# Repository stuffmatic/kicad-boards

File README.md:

# KiCad boards

This is a collection of mostly audio related dev boards designed in KiCad. The KiCad files are released under the [CC-BY-SA license](https://creativecommons.org/licenses/by-sa/4.0/).

## Board folders

Each board folder contains relevant datasheets along with [JLCPCB](https://jlcpcb.com/) fabrication files for PCB manufacturing and SMD assembly. Some additional easy hand soldering of connectors and headers may be required as indicated in the board description.

* [ap3722at\_mic\_breakout](ap3722at_mic_breakout) - Analog mono MEMS microphone breakout board.
* [bq24072\_pmic\_board](bq24072_pmic_board) - Power-path management and battery charger board.
* [pcm5102a\_codec\_breakout](pcm5102a_codec_breakout) - Audio codec breakout board.
* [tpa2012d2\_amp\_breakout](tpa2012d2_amp_breakout) - Class-D stereo audio power amplifier breakout board.
* [wm8758b\_codec\_breakout](wm8758b_codec_breakout) - Audio codec breakout board.
* [wm8904\_codec\_breakout](wm8904_codec_breakout) - Audio codec breakout board.

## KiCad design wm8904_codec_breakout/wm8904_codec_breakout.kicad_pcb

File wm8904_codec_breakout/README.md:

# WM8904 audio codec breakout board

A breakout board for the [WM8904 audio codec](datasheets/1912111437_Cirrus-Logic-WM8904CGEFL-RV_C323845.pdf) with 3.5mm microphone input and line/headphone output jacks.

## Pinout

* __VDD__ - Supply voltage,  3.3V - 12V 
* __GND__ - Ground
* __1V8__ - 1.8V codec supply voltage. Should typically not be connected.

See [datasheeet](datasheets/1912111437_Cirrus-Logic-WM8904CGEFL-RV_C323845.pdf) for the other pins.

## Connectors

* __MIC__ - Stereo microphone input
* __HP__ - Line/headphone output

## Hand soldered components

* 1x12 2.54 mm headers
* 1x12 2.54 mm headers

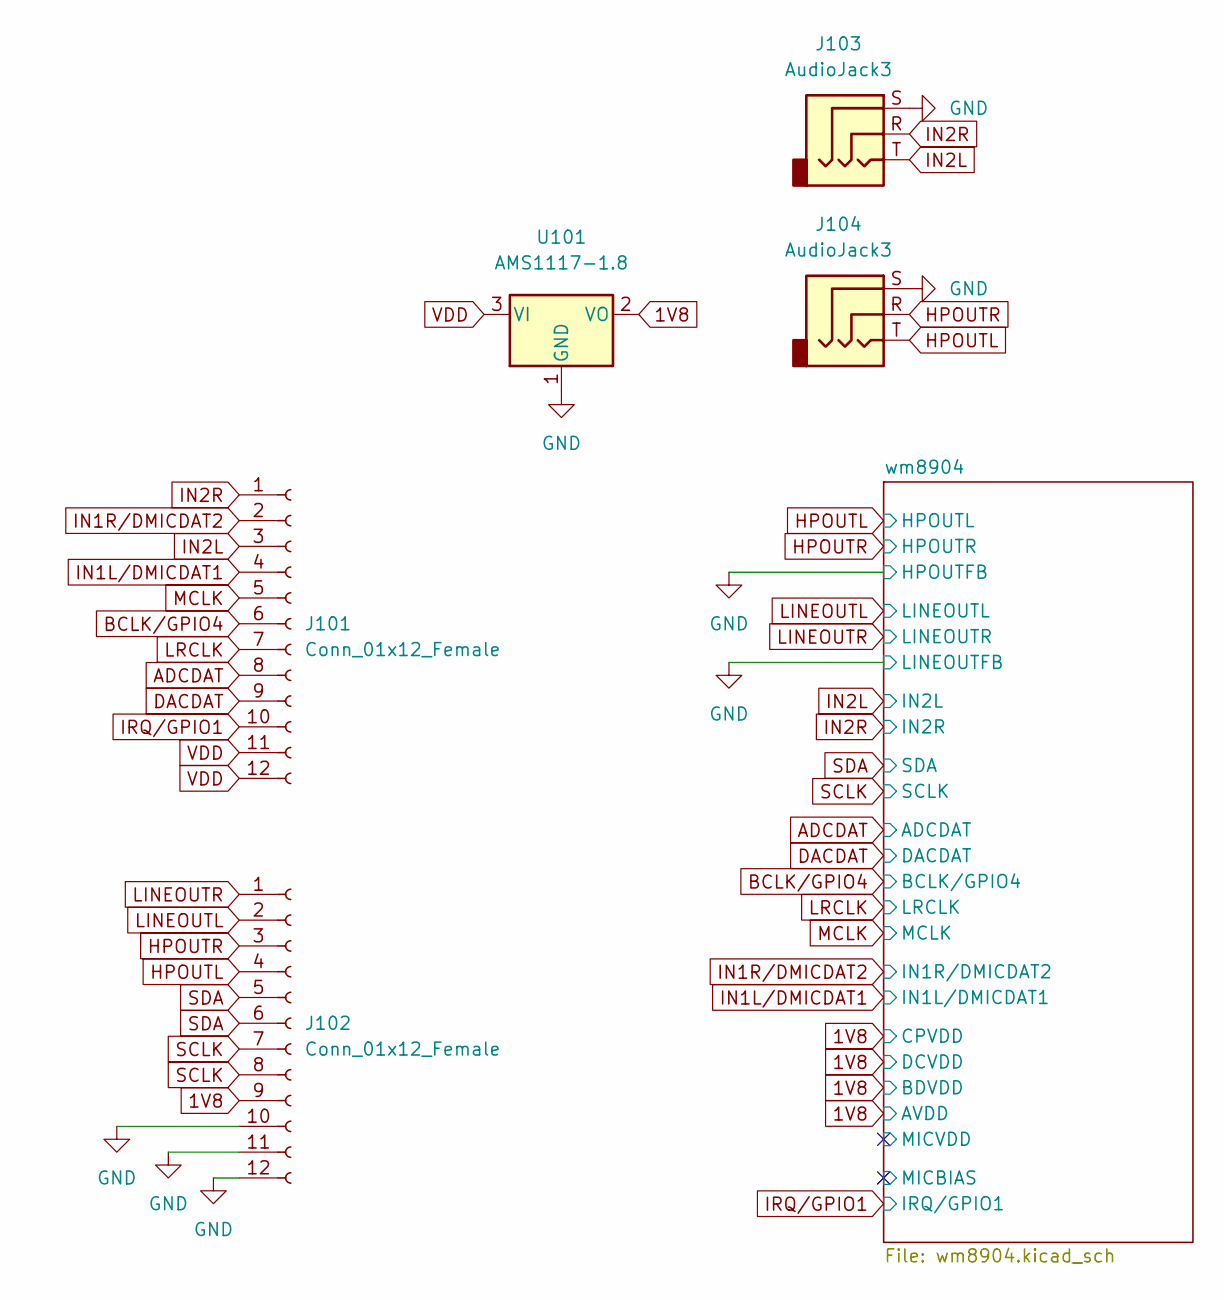
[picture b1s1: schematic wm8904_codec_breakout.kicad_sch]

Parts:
J101, J102: Conn_01x12_Female; PinSocket_1x12_P2.54mm_Vertical; JLCPCB BOM False
J103, J104: AudioJack3; PJ-320B-3A; LCSC Part C707224
U101: AMS1117-1.8; SOT-223-3_TabPin2; LCSC Part C6185

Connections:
1V8: J102.9, U101.2 (VO); also elsewhere on the board
ADCDAT: J101.8; also elsewhere on the board
BCLK/GPIO4: J101.6; also elsewhere on the board
DACDAT: J101.9; also elsewhere on the board
GND: J102.10, J102.11, J102.12, J103.S, J104.S, U101.1 (GND); also elsewhere on the board
HPOUTL: J102.4, J104.T; also elsewhere on the board
HPOUTR: J102.3, J104.R; also elsewhere on the board
IN1L/DMICDAT1: J101.4; also elsewhere on the board
IN1R/DMICDAT2: J101.2; also elsewhere on the board
IN2L: J101.3, J103.T; also elsewhere on the board
IN2R: J101.1, J103.R; also elsewhere on the board
IRQ/GPIO1: J101.10; also elsewhere on the board
LINEOUTL: J102.2; also elsewhere on the board
LINEOUTR: J102.1; also elsewhere on the board
LRCLK: J101.7; also elsewhere on the board
MCLK: J101.5; also elsewhere on the board
SCLK: J102.7, J102.8; also elsewhere on the board
SDA: J102.5, J102.6; also elsewhere on the board
VDD: J101.11, J101.12, U101.3 (VI)

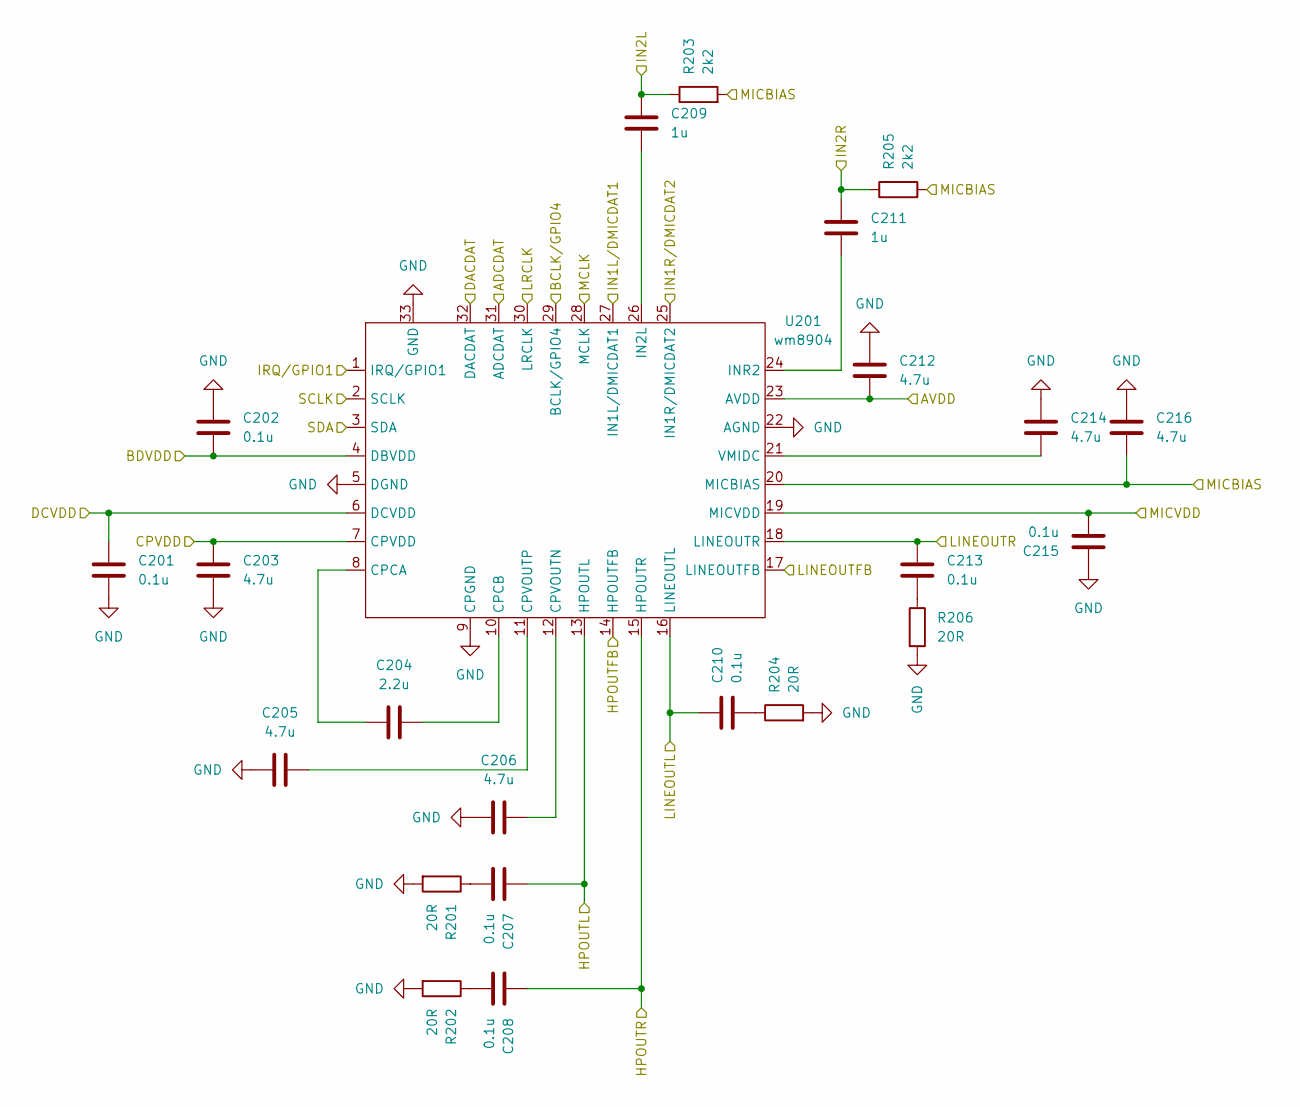
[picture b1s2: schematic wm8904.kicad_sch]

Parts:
C201, C202, C207, C208, C210, C213, C215: 0.1u; C_0402_1005Metric; LCSC Part C1525
C203, C205, C206, C212, C216: 4.7u; C_0402_1005Metric; LCSC Part C23733
C204: 2.2u; C_0402_1005Metric; LCSC Part C12530
C209, C211: 1u; C_0402_1005Metric; LCSC Part C52923
C214: 4.7u; C_0402_1005Metric; LCSC part C23733
R201, R202, R204, R206: 20R; R_0603_1608Metric; LCSC Part C22950
R203, R205: 2k2; R_0402_1005Metric; LCSC Part C25879
U201: wm8904; LCSC Part C323845

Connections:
1V8: C201.2, C202.2, C203.1, C212.2, U201.4 (DBVDD), U201.6 (DCVDD), U201.7 (CPVDD), U201.23 (AVDD); also elsewhere on the board
/wm8904/MICBIAS: C216.2, R203.2, R205.2, U201.20 (MICBIAS)
/wm8904/MICVDD: C215.2, U201.19 (MICVDD)
ADCDAT: U201.31 (ADCDAT); also elsewhere on the board
BCLK/GPIO4: U201.29 (BCLK/GPIO4); also elsewhere on the board
DACDAT: U201.32 (DACDAT); also elsewhere on the board
GND: C201.1, C202.1, C203.2, C205.1, C206.1, C212.1, C214.1, C215.1, C216.1, R201.2, R202.2, R204.2, R206.2, U201.5 (DGND), U201.9 (CPGND), U201.14 (HPOUTFB), U201.17 (LINEOUTFB), U201.22 (AGND), U201.33 (GND); also elsewhere on the board
HPOUTL: C207.1, U201.13 (HPOUTL); also elsewhere on the board
HPOUTR: C208.1, U201.15 (HPOUTR); also elsewhere on the board
IN1L/DMICDAT1: U201.27 (IN1L/DMICDAT1); also elsewhere on the board
IN1R/DMICDAT2: U201.25 (IN1R/DMICDAT2); also elsewhere on the board
IN2L: C209.1, R203.1; also elsewhere on the board
IN2R: C211.1, R205.1; also elsewhere on the board
IRQ/GPIO1: U201.1 (IRQ/GPIO1); also elsewhere on the board
LINEOUTL: C210.1, U201.16 (LINEOUTL); also elsewhere on the board
LINEOUTR: C213.1, U201.18 (LINEOUTR); also elsewhere on the board
LRCLK: U201.30 (LRCLK); also elsewhere on the board
MCLK: U201.28 (MCLK); also elsewhere on the board
unnamed: C204.1, U201.8 (CPCA)
unnamed: C204.2, U201.10 (CPCB)
unnamed: C205.2, U201.11 (CPVOUTP)
unnamed: C206.2, U201.12 (CPVOUTN)
unnamed: C207.2, R201.1
unnamed: C208.2, R202.1
unnamed: C209.2, U201.26 (IN2L)
unnamed: C210.2, R204.1
unnamed: C211.2, U201.24 (INR2)
unnamed: C213.2, R206.1
unnamed: C214.2, U201.21 (VMIDC)
SCLK: U201.2 (SCLK); also elsewhere on the board
SDA: U201.3 (SDA); also elsewhere on the board

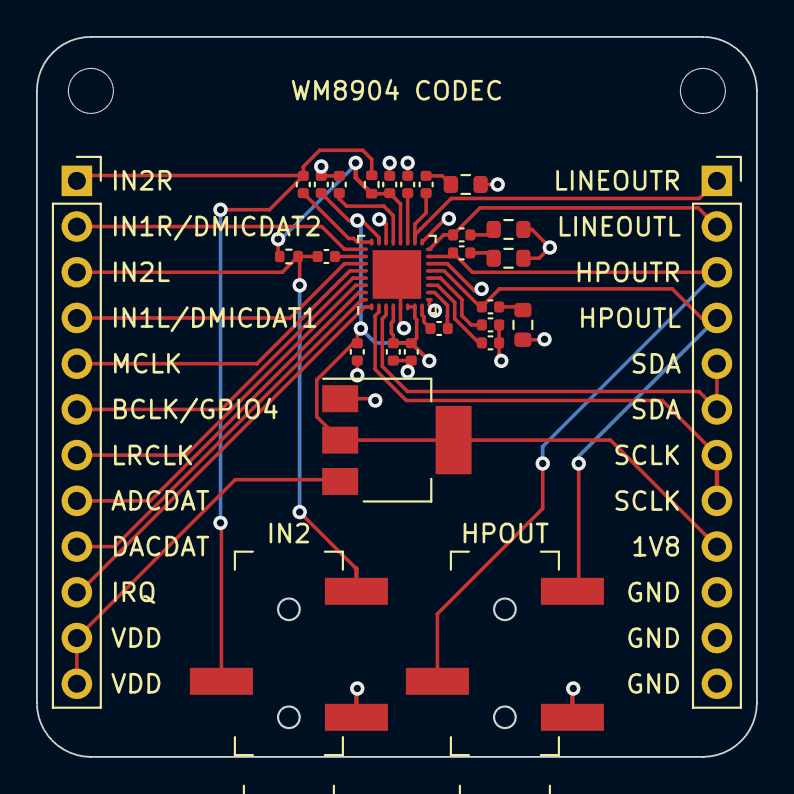
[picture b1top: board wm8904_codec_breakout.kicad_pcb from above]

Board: 2 copper layers, 40.0 x 40.0 mm, 28 parts (0 on the bottom side), 32 nets.

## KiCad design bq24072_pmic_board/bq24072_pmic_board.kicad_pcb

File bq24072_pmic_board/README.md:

# BQ24072 PMIC board

A USB LiPo battery charger and power-path management board based on [Texas Instruments BQ24072](datasheets/1806131014_Texas-Instruments-BQ24072RGTR_C140288.pdf).

## Pinout

* __VBUS__ - 5V USB bus voltage
* __D-, D+__ - USB data lines
* __3V3__ - 3.3V output voltage 
* __GND__ - Ground

## Connectors

* __BAT__ - LiPo battery. Refer to the + indication to ensure  correct polarity.

## LEDs

* __VUSB__ - USB bus voltage present
* __CHG__ - Charging status indication
* __PGOOD__ - Power good status indication

## Hand soldered components

* 1x5 2.54 mm headers
* 2-pin, 2.0 mm pitch, horizontal JST PH connector (**BAT**)

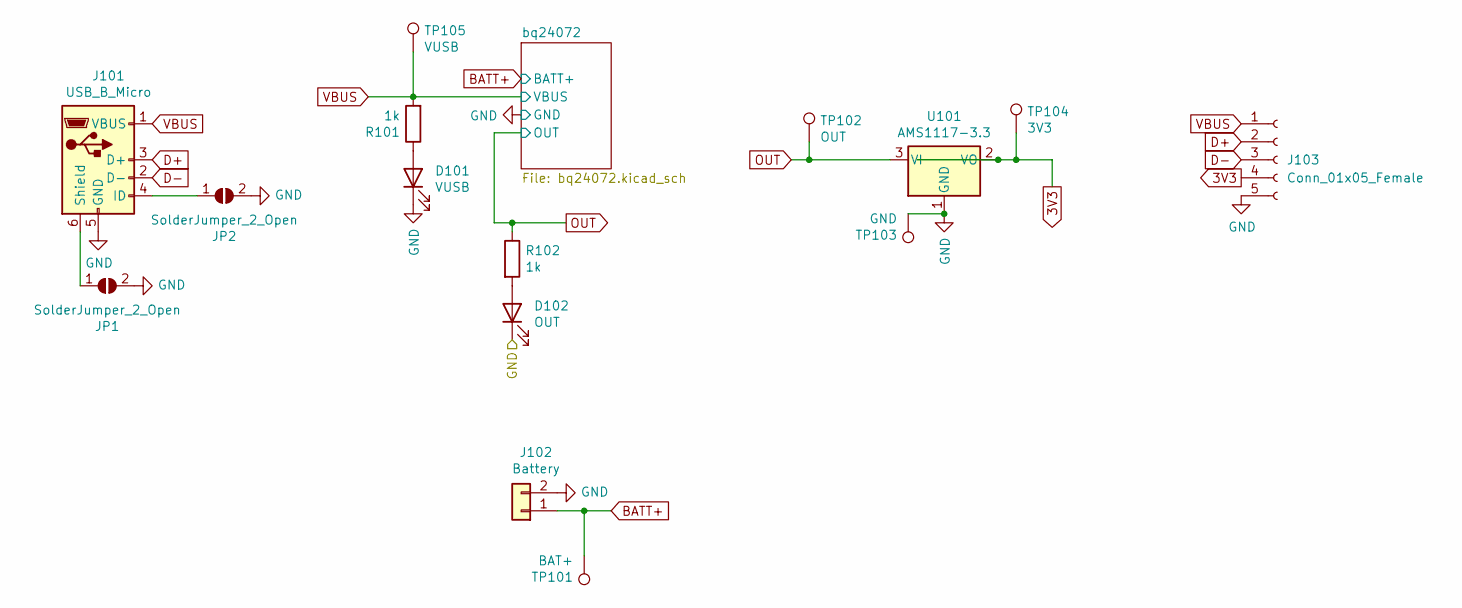
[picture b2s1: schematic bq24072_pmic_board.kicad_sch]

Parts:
D101: VUSB; LED_0603_1608Metric; LCSC Part C72043
D102: OUT; LED_0603_1608Metric; LCSC Part C72043
J101: USB_B_Micro; USB_Micro-AB_Molex_47590-0001; LCSC Part C136001
J102: Battery; JST_PH_S2B-PH-K_1x02_P2.00mm_Horizontal; JLCPCB BOM False
J103: Conn_01x05_Female; PinSocket_1x05_P2.54mm_Vertical; JLCPCB BOM False
JP1, JP2: SolderJumper_2_Open; SolderJumper-2_P1.3mm_Open_RoundedPad1.0x1.5mm; JLCPCB BOM False
R101, R102: 1k; R_0603_1608Metric; LCSC Part C21190
TP101: BAT+; TestPoint_Pad_D2.0mm; JLCPCB BOM False
TP102: OUT; TestPoint_Pad_D2.0mm; JLCPCB BOM False
TP103: GND; TestPoint_Pad_D2.0mm; JLCPCB BOM False
TP104: 3V3; TestPoint_Pad_D2.0mm; JLCPCB BOM False
TP105: VUSB; TestPoint_Pad_D2.0mm; JLCPCB BOM False
U101: AMS1117-3.3; SOT-223-3_TabPin2; LCSC Part C6186

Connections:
3V3: J103.4, TP104.1, U101.2 (VO)
BATT+: J102.1, TP101.1; also elsewhere on the board
D+: J101.3 (D+), J103.2
D-: J101.2 (D-), J103.3
GND: D101.1 (K), D102.1 (K), J101.5 (GND), J102.2, J103.5, JP1.2 (B), JP2.2 (B), TP103.1, U101.1 (GND); also elsewhere on the board
unnamed: D101.2 (A), R101.1
unnamed: D102.2 (A), R102.2
unnamed: J101.4 (ID), JP2.1 (A)
unnamed: J101.6 (Shield), JP1.1 (A)
OUT: R102.1, TP102.1, U101.3 (VI); also elsewhere on the board
VBUS: J101.1 (VBUS), J103.1, R101.2, TP105.1; also elsewhere on the board

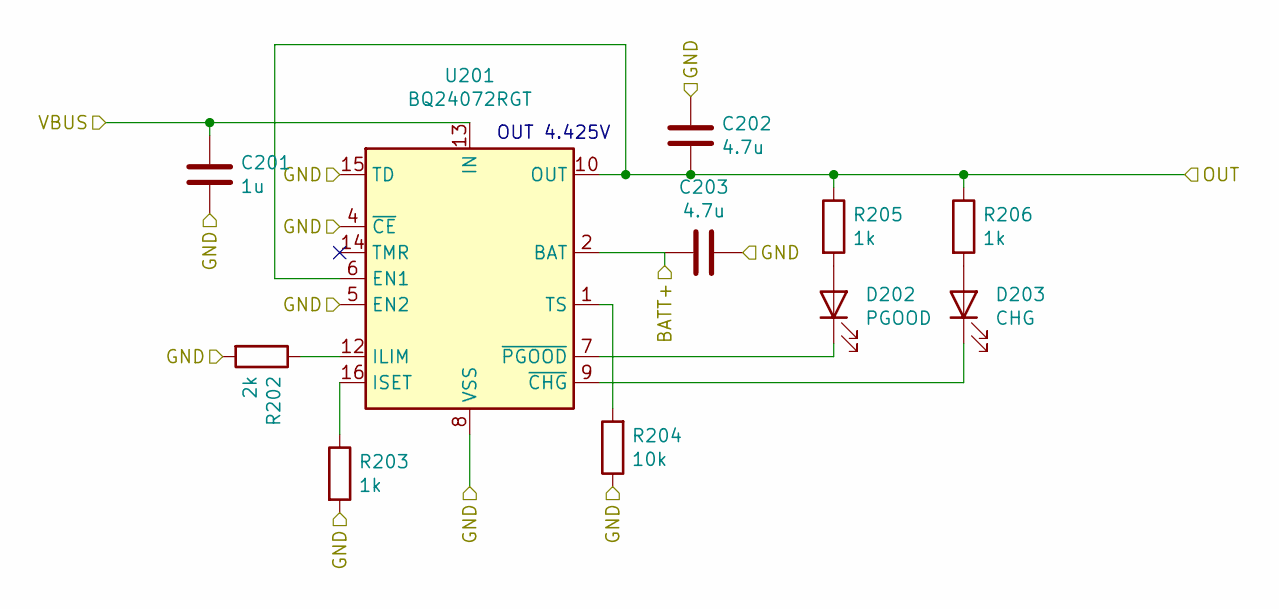
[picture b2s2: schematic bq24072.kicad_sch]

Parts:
C201: 1u; C_0603_1608Metric; LCSC Part C15849
C202, C203: 4.7u; C_0603_1608Metric; LCSC Part C19666
D202: PGOOD; LED_0603_1608Metric; LCSC Part C72043
D203: CHG; LED_0805_2012Metric; LCSC Part C84256
R202: 2k; R_0603_1608Metric; LCSC Part C22975
R203, R205, R206: 1k; R_0603_1608Metric; LCSC Part C21190
R204: 10k; R_0603_1608Metric; LCSC Part C25804
U201: BQ24072RGT; VQFN-16-1EP_3x3mm_P0.5mm_EP1.6x1.6mm; LCSC Part C140288

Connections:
BATT+: C203.2, U201.2 (BAT), U201.3 (BAT); also elsewhere on the board
GND: C201.2, C202.1, C203.1, R202.2, R203.2, R204.1, U201.4 (~CE), U201.5 (EN2), U201.8 (VSS), U201.15 (TD), U201.17 (VSS); also elsewhere on the board
unnamed: D202.1 (K), U201.7 (~PGOOD)
unnamed: D202.2 (A), R205.2
unnamed: D203.1 (K), U201.9 (~CHG)
unnamed: D203.2 (A), R206.2
unnamed: R202.1, U201.12 (ILIM)
unnamed: R203.1, U201.16 (ISET)
unnamed: R204.2, U201.1 (TS)
OUT: C202.2, R205.1, R206.1, U201.6 (EN1), U201.10 (OUT), U201.11 (OUT); also elsewhere on the board
VBUS: C201.1, U201.13 (IN); also elsewhere on the board

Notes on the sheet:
OUT 4.425V

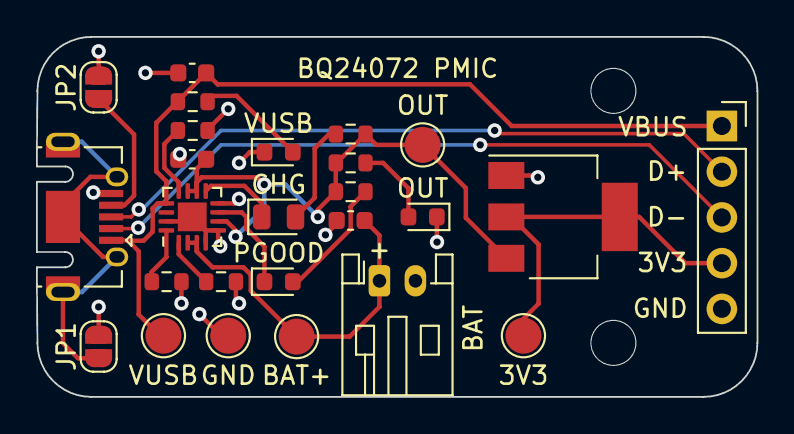
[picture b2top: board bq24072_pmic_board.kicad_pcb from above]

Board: 2 copper layers, 40.0 x 20.0 mm, 26 parts (0 on the bottom side), 18 nets.

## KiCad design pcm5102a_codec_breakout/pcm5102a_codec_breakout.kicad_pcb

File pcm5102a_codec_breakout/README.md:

# PCM5102A audio codec breakout board

A breakout board for the [PCM5102A audio codec](datasheets/pcm5102a-q1.pdf) with a 3.5mm line out jack.

## Pinout

* **GND** - Ground
* **VDD** - 3.3V supply voltage

See [datasheeet](datasheets/pcm5102a-q1.pdf) for the other pins.

## Connectors

* __LINE OUT__ - Line level output (not suitable for headphones)

## Hand soldered components

* 1x7 2.54 mm headers

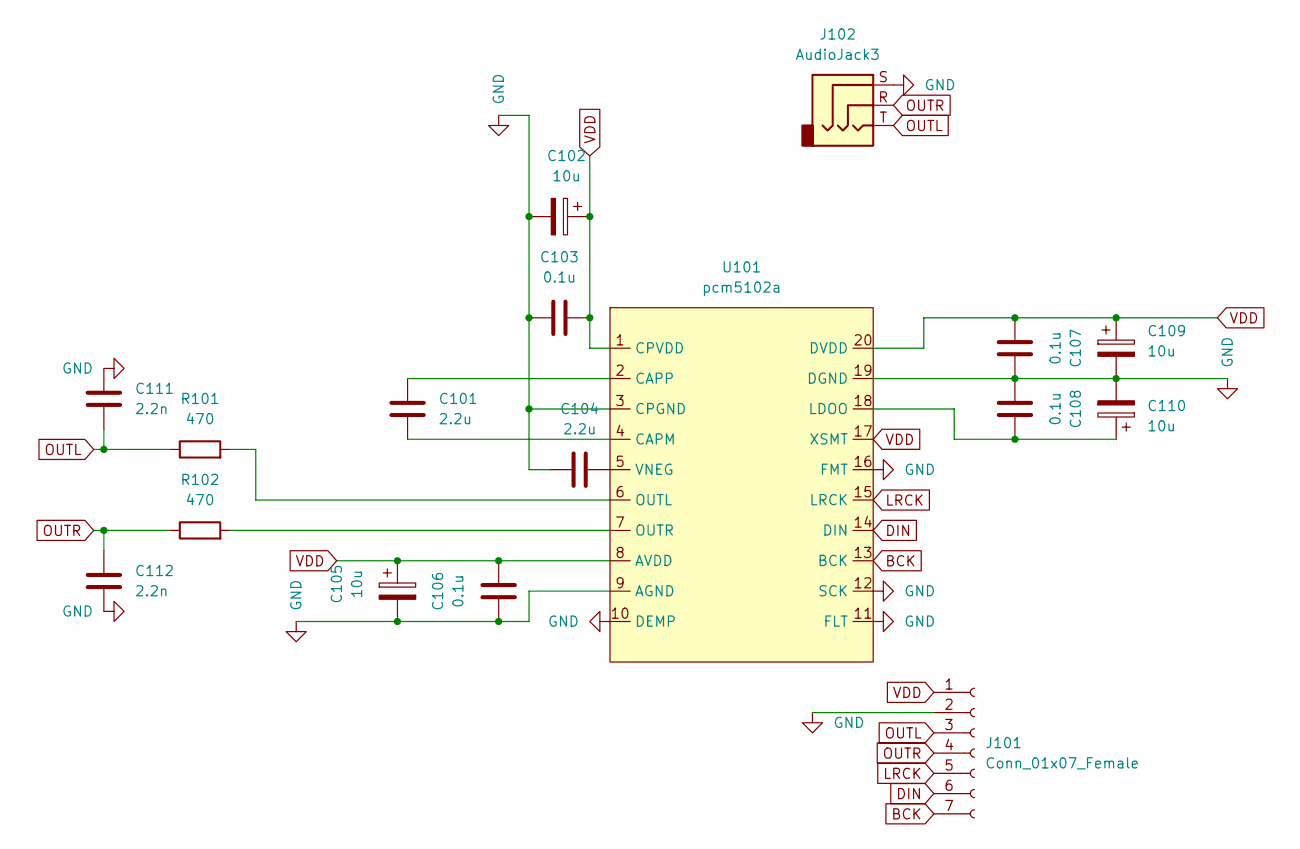
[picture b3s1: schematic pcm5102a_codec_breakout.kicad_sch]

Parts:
C101, C104: 2.2u; C_0402_1005Metric; LCSC Part C12530
C102, C105, C109, C110: 10u; C_Elec_4x5.4; LCSC Part C213487
C103, C106, C107, C108: 0.1u; C_0402_1005Metric; LCSC Part C1525
C111, C112: 2.2n; C_0402_1005Metric; LCSC Part C1531
J101: Conn_01x07_Female; PinHeader_1x07_P2.54mm_Vertical; JLCPCB BOM False
J102: AudioJack3; PJ-320B-3A; LCSC Part C707224
R101, R102: 470; R_0402_1005Metric; LCSC Part C25117
U101: pcm5102a; PCM5102A; LCSC Part C107671

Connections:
BCK: J101.7, U101.13 (BCK)
DIN: J101.6, U101.14 (DIN)
GND: C102.2, C103.1, C104.1, C105.2, C106.1, C107.2, C108.1, C109.2, C110.2, C111.2, C112.1, J101.2, J102.S, U101.3 (CPGND), U101.9 (AGND), U101.10 (DEMP), U101.11 (FLT), U101.12 (SCK), U101.16 (FMT), U101.19 (DGND)
LRCK: J101.5, U101.15 (LRCK)
unnamed: C101.1, U101.2 (CAPP)
unnamed: C101.2, U101.4 (CAPM)
unnamed: C104.2, U101.5 (VNEG)
unnamed: C108.2, C110.1, U101.18 (LDOO)
unnamed: R101.2, U101.6 (OUTL)
unnamed: R102.2, U101.7 (OUTR)
OUTL: C111.1, J101.3, J102.T, R101.1
OUTR: C112.2, J101.4, J102.R, R102.1
VDD: C102.1, C103.2, C105.1, C106.2, C107.1, C109.1, J101.1, U101.1 (CPVDD), U101.8 (AVDD), U101.17 (XSMT), U101.20 (DVDD)

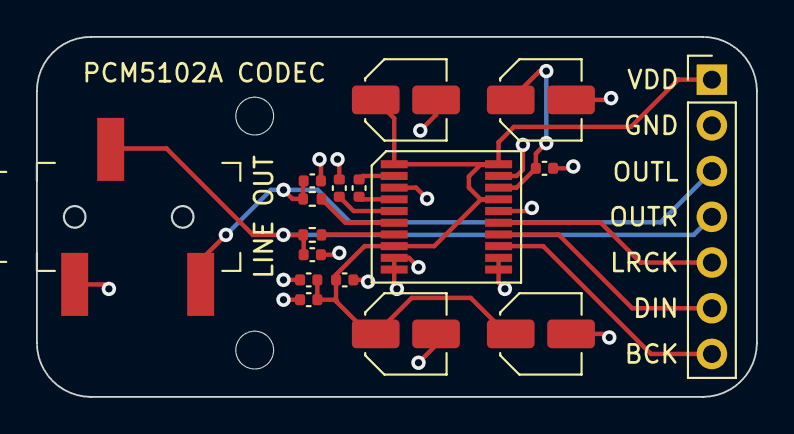
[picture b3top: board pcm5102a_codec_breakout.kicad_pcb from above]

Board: 2 copper layers, 40.0 x 20.0 mm, 17 parts (0 on the bottom side), 13 nets.

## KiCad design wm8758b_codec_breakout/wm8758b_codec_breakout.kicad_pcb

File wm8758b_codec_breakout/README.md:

# WM8758b audio codec breakout board

⚠️ __Warning:__ The WM8758b has been [discontinued](https://www.cirrus.com/products/eol/).

A breakout board for the [WM8758b audio codec](datasheets/1811051126_Cirrus-Logic-WM8758CBGEFL-RV_C323840.pdf) with 3.5mm microphone input and line/headphone output jacks.

## Pinout

* __VDD__ - 3.3V supply voltage
* __GND__ - Ground

See [datasheeet](datasheets/1811051126_Cirrus-Logic-WM8758CBGEFL-RV_C323840.pdf) for the other pins.

## Connectors

* __MIC__ - Stereo microphone input
* __HP__ - Line/headphone output

## Hand soldered components

* 1x12 2.54 mm headers
* 1x12 2.54 mm headers

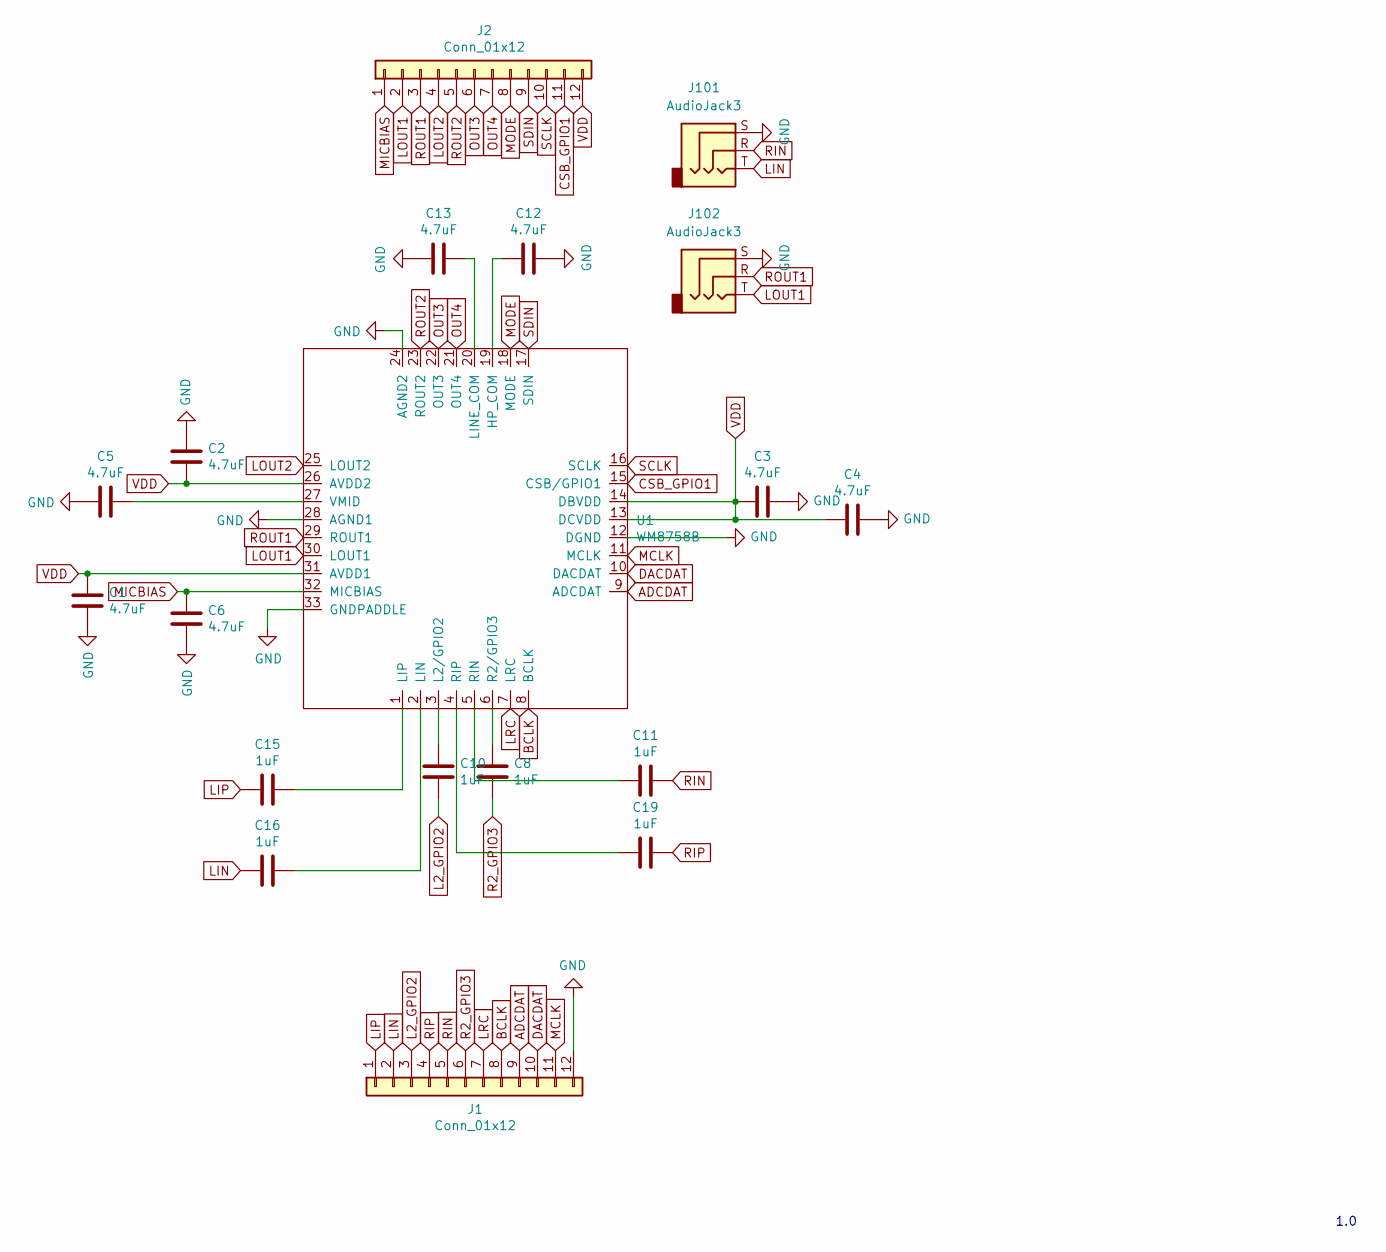
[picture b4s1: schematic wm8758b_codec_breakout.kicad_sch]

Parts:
C1, C2, C3, C4, C5, C6, C12, C13: 4.7uF; C_0603_1608Metric; LCSC Part C19666
C8, C10, C11, C15, C16, C19: 1uF; C_0603_1608Metric; LCSC Part C15849
J1, J2: Conn_01x12; PinSocket_1x12_P2.54mm_Vertical; JLCPCB BOM False
J101, J102: AudioJack3; PJ-320B-3A; LCSC Part C707224
U1: WM8758B; LCSC Part C323840

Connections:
ADCDAT: J1.9, U1.9 (ADCDAT)
BCLK: J1.8, U1.8 (BCLK)
CSB_GPIO1: J2.11, U1.15 (CSB/GPIO1)
DACDAT: J1.10, U1.10 (DACDAT)
GND: C1.2, C2.2, C3.1, C4.1, C5.2, C6.2, C12.1, C13.2, J1.12, J101.S, J102.S, U1.12 (DGND), U1.24 (AGND2), U1.28 (AGND1), U1.33 (GNDPADDLE)
L2_GPIO2: C10.2, J1.3
LIN: C16.2, J1.2, J101.T
LIP: C15.2, J1.1
LOUT1: J2.2, J102.T, U1.30 (LOUT1)
LOUT2: J2.4, U1.25 (LOUT2)
LRC: J1.7, U1.7 (LRC)
MCLK: J1.11, U1.11 (MCLK)
MICBIAS: C6.1, J2.1, U1.32 (MICBIAS)
MODE: J2.8, U1.18 (MODE)
unnamed: C5.1, U1.27 (VMID)
unnamed: C8.1, U1.6 (R2/GPIO3)
unnamed: C10.1, U1.3 (L2/GPIO2)
unnamed: C11.2, U1.5 (RIN)
unnamed: C12.2, U1.19 (HP_COM)
unnamed: C13.1, U1.20 (LINE_COM)
unnamed: C15.1, U1.1 (LIP)
unnamed: C16.1, U1.2 (LIN)
unnamed: C19.2, U1.4 (RIP)
OUT3: J2.6, U1.22 (OUT3)
OUT4: J2.7, U1.21 (OUT4)
R2_GPIO3: C8.2, J1.6
RIN: C11.1, J1.5, J101.R
RIP: C19.1, J1.4
ROUT1: J2.3, J102.R, U1.29 (ROUT1)
ROUT2: J2.5, U1.23 (ROUT2)
SCLK: J2.10, U1.16 (SCLK)
SDIN: J2.9, U1.17 (SDIN)
VDD: C1.1, C2.1, C3.2, C4.2, J2.12, U1.13 (DCVDD), U1.14 (DBVDD), U1.26 (AVDD2), U1.31 (AVDD1)

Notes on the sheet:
1.0

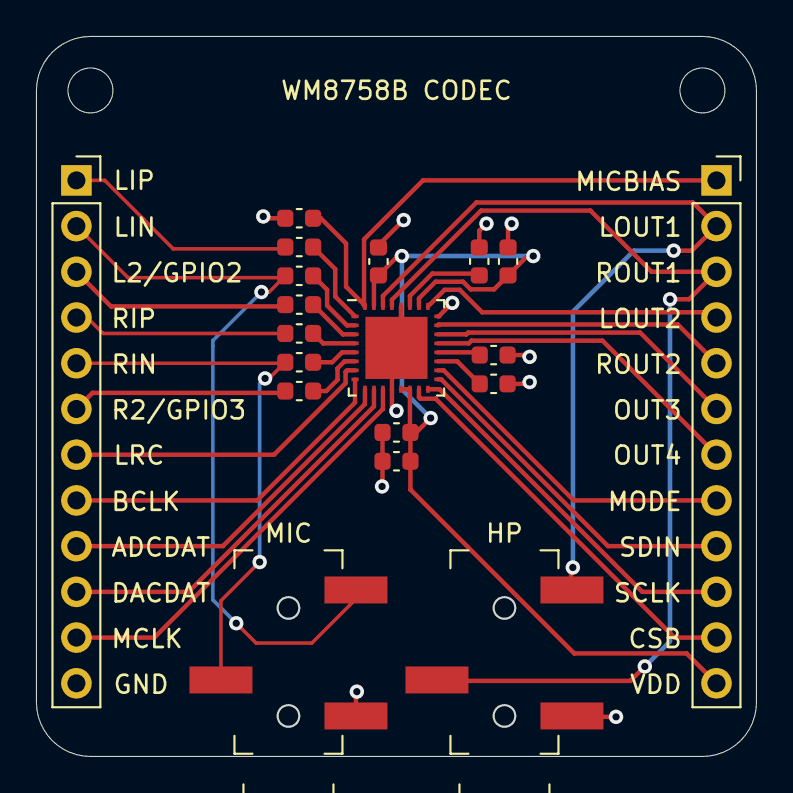
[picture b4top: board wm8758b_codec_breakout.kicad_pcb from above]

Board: 2 copper layers, 39.9 x 39.9 mm, 19 parts (0 on the bottom side), 33 nets.

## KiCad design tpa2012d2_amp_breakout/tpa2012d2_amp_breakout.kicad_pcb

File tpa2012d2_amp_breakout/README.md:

# TPA2012D2 breakout board

A [TPA2012D2](datasheets/1809121818_Texas-Instruments-TPA2012D2RTJR_C7717.pdf) class-D stereo audio power amplifier breakout board with a 3.5mm line input jack.

## Pinout

* __GND__ - Ground
* __INL__ and __INR__ - Left and right channel line input. May be used instead of the line input jack.
* __VDD__ - Supply voltage, 2.5V - 5.5V recommended

The __G0__ and __G1__ jumpers control the output gain and the  __SD__ jumper controls the __SDL__ and __SDR__ channel shutdown pins, see [datasheet](datasheets/1809121818_Texas-Instruments-TPA2012D2RTJR_C7717.pdf).

## Connectors

* __SPK L__ - Left speaker output
* __SPK R__ - Right speaker output
* __IN__ - Stereo line input

## Hand soldered components

* 1x4 2.54mm headers
* 1x3 2.54mm headers (__G0__)
* 1x3 2.54mm headers (__G1__)
* 1x3 2.54mm headers (__SD__)
* 2-pin, 2.0 mm pitch, horizontal JST PH connector (**SPK L**)
* 2-pin, 2.0 mm pitch, horizontal JST PH connector (**SPK R**)

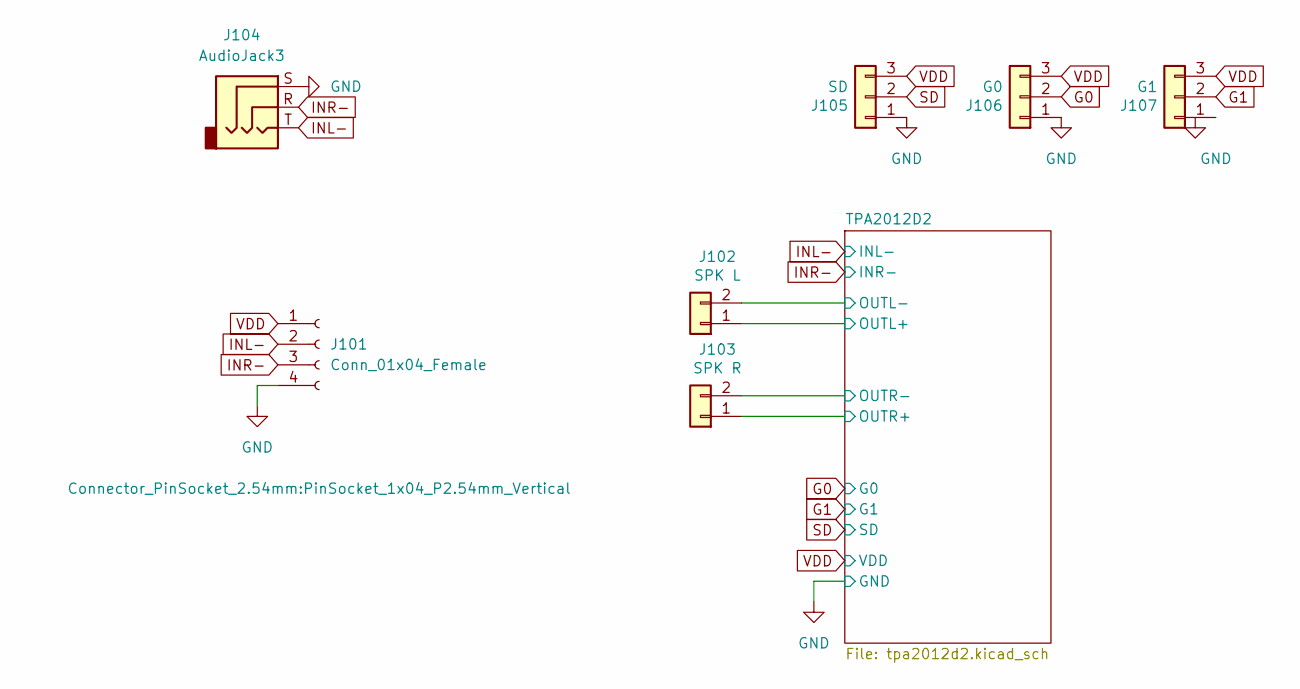
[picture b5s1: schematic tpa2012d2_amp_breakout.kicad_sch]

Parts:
J101: Conn_01x04_Female; PinSocket_1x04_P2.54mm_Vertical; JLCPCB BOM False
J102: SPK L; JST_PH_S2B-PH-K_1x02_P2.00mm_Horizontal; JLCPCB BOM False
J103: SPK R; JST_PH_S2B-PH-K_1x02_P2.00mm_Horizontal; JLCPCB BOM False
J104: AudioJack3; PJ-320B-3A; LCSC Part C707224
J105: SD; PinHeader_1x03_P2.54mm_Vertical; JLCPCB BOM False
J106: G0; PinHeader_1x03_P2.54mm_Vertical; JLCPCB BOM False
J107: G1; PinHeader_1x03_P2.54mm_Vertical; JLCPCB BOM False

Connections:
/TPA2012D2/OUTL+: J102.1; also elsewhere on the board
/TPA2012D2/OUTL-: J102.2; also elsewhere on the board
/TPA2012D2/OUTR+: J103.1; also elsewhere on the board
/TPA2012D2/OUTR-: J103.2; also elsewhere on the board
G0: J106.2; also elsewhere on the board
G1: J107.2; also elsewhere on the board
GND: J101.4, J104.S, J105.1, J106.1; also elsewhere on the board
INL-: J101.2, J104.T; also elsewhere on the board
INR-: J101.3, J104.R; also elsewhere on the board
SD: J105.2; also elsewhere on the board
VDD: J101.1, J105.3, J106.3, J107.3; also elsewhere on the board

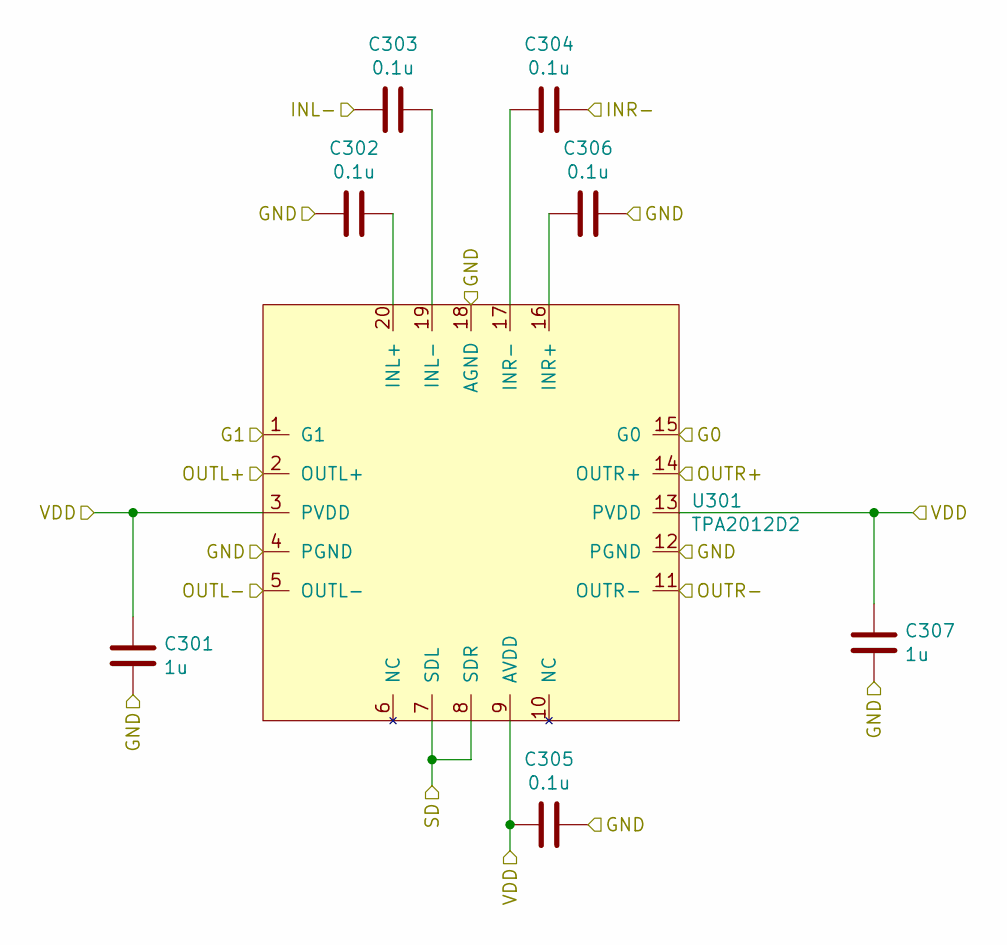
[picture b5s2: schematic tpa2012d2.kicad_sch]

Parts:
C301, C307: 1u; C_0603_1608Metric; LCSC Part C15849
C302, C303, C304, C305, C306: 0.1u; C_0603_1608Metric; LCSC Part C14663
U301: TPA2012D2; LCSC Part C7717

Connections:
/TPA2012D2/OUTL+: U301.2 (OUTL+); also elsewhere on the board
/TPA2012D2/OUTL-: U301.5 (OUTL-); also elsewhere on the board
/TPA2012D2/OUTR+: U301.14 (OUTR+); also elsewhere on the board
/TPA2012D2/OUTR-: U301.11 (OUTR-); also elsewhere on the board
G0: U301.15 (G0); also elsewhere on the board
G1: U301.1 (G1); also elsewhere on the board
GND: C301.2, C302.2, C305.1, C306.2, C307.2, U301.4 (PGND), U301.12 (PGND), U301.18 (AGND); also elsewhere on the board
INL-: C303.2; also elsewhere on the board
INR-: C304.1; also elsewhere on the board
unnamed: C302.1, U301.20 (INL+)
unnamed: C303.1, U301.19 (INL-)
unnamed: C304.2, U301.17 (INR-)
unnamed: C306.1, U301.16 (INR+)
SD: U301.7 (SDL), U301.8 (SDR); also elsewhere on the board
VDD: C301.1, C305.2, C307.1, U301.3 (PVDD), U301.9 (AVDD), U301.13 (PVDD); also elsewhere on the board

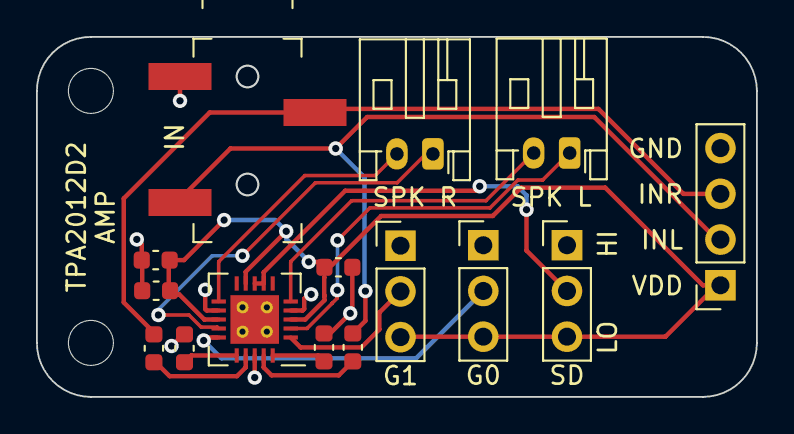
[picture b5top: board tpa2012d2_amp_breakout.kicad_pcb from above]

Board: 2 copper layers, 40.0 x 20.0 mm, 15 parts (0 on the bottom side), 15 nets.

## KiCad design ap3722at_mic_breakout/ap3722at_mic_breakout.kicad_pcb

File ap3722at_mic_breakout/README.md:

# AP3722AT MEMS microphone breakout

A breakout board for the [AP3722AT](datasheets/2011200934_ALLPOWER-ShenZhen-Quan-Li-Semiconductor-AP3722AT_C918198.pdf) analog mono MEMS microphone.

## Pinout

See [datasheet](datasheets/2011200934_ALLPOWER-ShenZhen-Quan-Li-Semiconductor-AP3722AT_C918198.pdf).

## Hand soldered components

* 1x3 2.54 mm headers

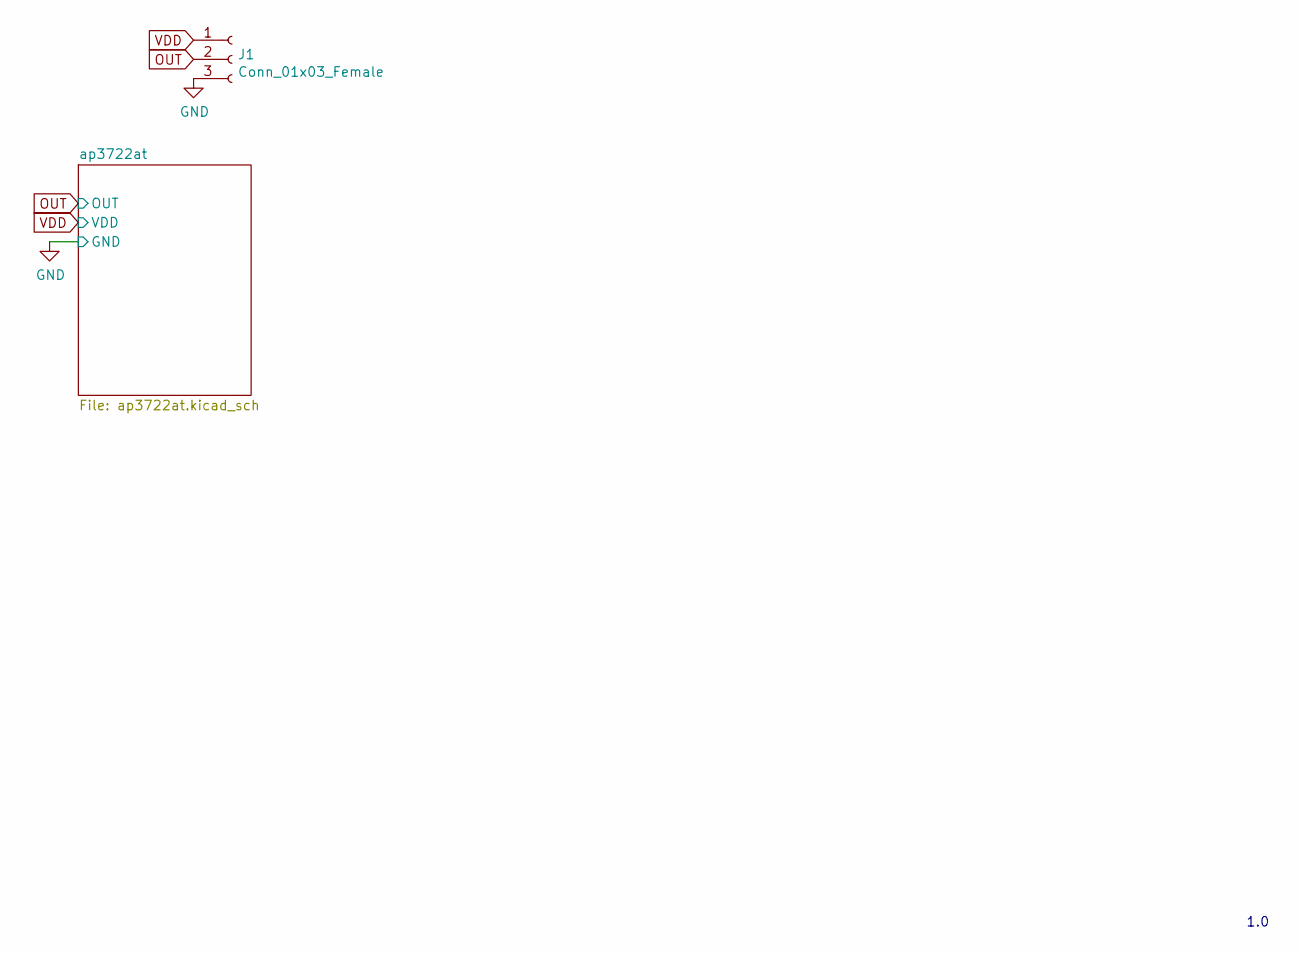
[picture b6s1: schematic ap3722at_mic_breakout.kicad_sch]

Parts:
J1: Conn_01x03_Female; PinHeader_1x03_P2.54mm_Vertical; JLCPCB BOM False

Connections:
GND: J1.3; also elsewhere on the board
OUT: J1.2; also elsewhere on the board
VDD: J1.1; also elsewhere on the board

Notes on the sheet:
1.0

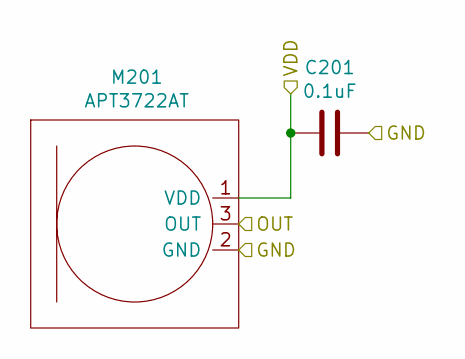
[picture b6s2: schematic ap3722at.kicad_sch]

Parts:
C201: 0.1uF; C_0603_1608Metric; LCSC Part C14663
M201: APT3722AT; AP3722AT; LCSC Part C918198

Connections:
GND: C201.1, M201.2 (GND); also elsewhere on the board
OUT: M201.3 (OUT); also elsewhere on the board
VDD: C201.2, M201.1 (VDD); also elsewhere on the board

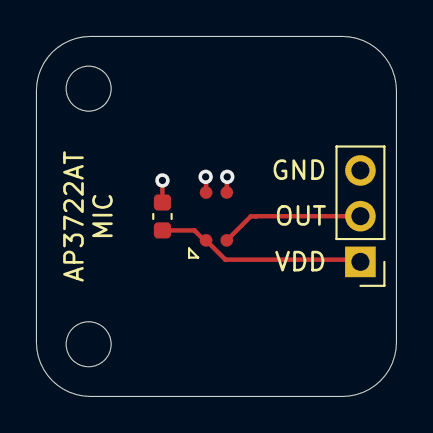
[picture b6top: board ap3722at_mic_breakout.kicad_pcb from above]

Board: 2 copper layers, 20.0 x 20.0 mm, 3 parts (0 on the bottom side), 3 nets.

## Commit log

2022-08-17 [bq24072_pmic_board] Use hierarchical sheet for bq24072
2022-08-17 [bq24072_pmic_board] Move some LEDs from the hierarchical sheet
2022-08-17 [bq24072_pmic_board] Use 1k LED resistors
2022-08-17 final touches + v1 jlcpcb fab files
2022-08-17 Fix PJ-320B-3A footprint
2022-08-17 Order JLCPC V1
2022-08-17 add JLCPCB gerber zip files
2022-08-29 [wm8904_codec_breakout] Fix silkscreen typo (change LINEOUTFL to LINEOUTL)
2022-08-30 [wm8904_codec_breakout] Tighter ground plane filled zone boundary
2022-11-10 first pass on documentation
2022-11-10 doc tweaks
2022-11-11 [bq24072_pmic_board] Add VBUS output and bump board revision to v2
2022-11-24 [pcm5102a_codec_breakout] First pass on routing
2022-11-24 [pcm5102a_codec_breakout] Schematic fixes and re-routing
2022-11-25 [pcm5102a_codec_breakout] Tweaks and fixes
2022-11-25 [pcm5102a_codec_breakout] V1 JLCPCB fab files
2022-11-25 [wm8758b_codec_breakout] remove unused files
2022-11-25 [bq24072_pmic_board] V2 JLCPCB fab files
2022-11-25 [bq24072_pmic_board] v2 fab file tweaks
2022-11-27 [wm8904_codec_breakout] connect LINEOUTFB and HPOUTFB to ground and bump board version to v2
2022-11-28 [wm8904_codec_breakout] Add v2 fabrication files
2022-11-28 [wm8904_codec_breakout] Silkscreen label fixes
2023-01-16 Board description fixes
